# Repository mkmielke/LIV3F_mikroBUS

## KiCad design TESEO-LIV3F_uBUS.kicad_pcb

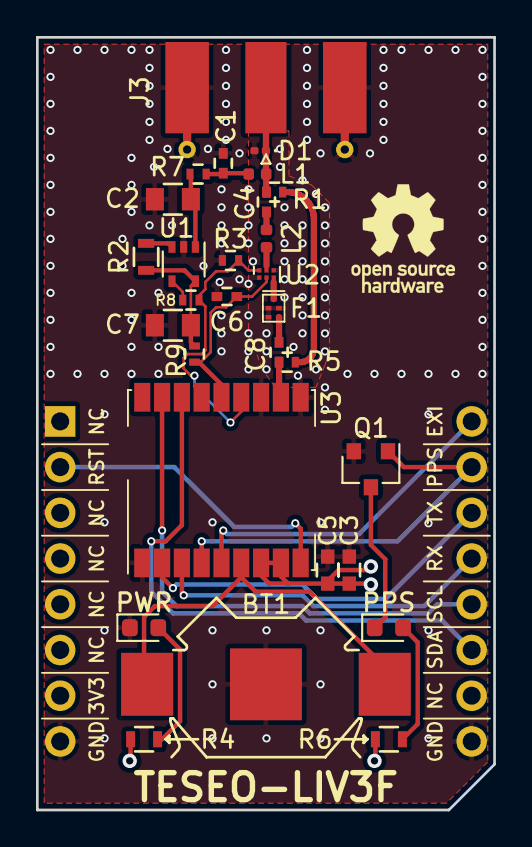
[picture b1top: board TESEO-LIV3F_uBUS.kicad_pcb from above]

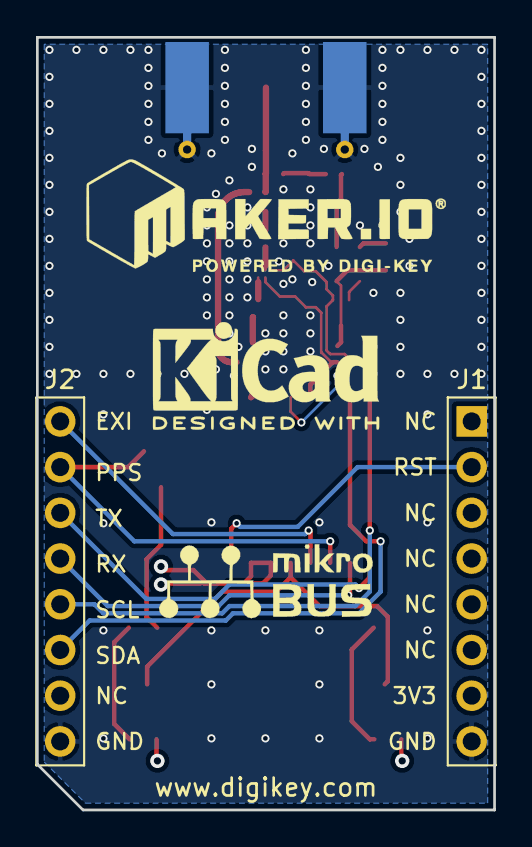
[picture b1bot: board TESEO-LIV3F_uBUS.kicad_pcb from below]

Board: 4 copper layers, 25.4 x 42.9 mm, 31 parts (2 on the bottom side), 27 nets.

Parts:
BT1: Battery_Cell; Keystone_3030_1x10mm-CoinCell
C1: 56p; C_0402
C2: 1u; C_0805
C3: 100p; C_0603
C4, C8: 120p; C_0402
C5: 100n; C_0603
C6: 1n; C_0402
C7: 2.2u; C_0805
D1: D_TVS_ALT; D_0201_0603Metric
D2: LTST-C190KGKT; D_0603_1608Metric
D3: LTST-C190KRKT; D_0603_1608Metric
F1: B4327; Filter_1411-5_1.4x1.1mm
J1, J2: Conn_01x08; PinHeader_1x08_P2.54mm_Vertical
J3: Conn_Coaxial; SMA_Molex_73251-1153_EdgeMount_Horizontal
L1: 56n; L_0402_1005Metric
L2: 6.8n; L_0402_1005Metric
Q1: MMUN2211LT1G; SOT-23
R1, R5, R7, R8, R9: 0; R_0402
R2: 100k; R_0603
R3: 10k; R_0402
R4, R6: 330; R_0603
U1: TPS22943; SOT-353_SC-70-5
U2: BGA725L6; TSNP-6_0.8x0.7mm_P0.4mm
U3: TESEO-LIV3F; TESEO_LIV3F_SMD

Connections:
+3V3: C3.2, C5.2, J1.7, R4.1, R6.1, U3.7, U3.8
+BATT: BT1.1, U3.6
/ANT_OFF: R3.2, R8.2, U2.6, U3.13
/EXI: J2.1, U3.5
/PPS: J2.2, Q1.1, U3.4
/RESET: J1.2, U3.9
/RF_IN: C8.1, R5.1, U3.11
/RX: J2.4, U3.3
/SCL: J2.5, U3.17
/SDA: J2.6, U3.16
/TX: J2.3, U3.2
/VCC_RF: C6.1, R9.2, U2.2, U3.14
GND: BT1.2, C1.2, C2.2, C3.1, C5.1, C6.2, C7.2, D1.2, D2.1, F1.2, F1.3, F1.5, J1.8, J2.8, J3.2, Q1.2, R3.1, U1.2, U2.1, U2.4, U3.1, U3.10, U3.12
unnamed: C1.1, L1.2, R7.2
unnamed: C2.1, R7.1, U1.1
unnamed: C4.1, L2.2
unnamed: C4.2, D1.1, J3.1, L1.1, R1.1
unnamed: C7.1, R2.1, R9.1, U1.5
unnamed: C8.2, F1.4
unnamed: D2.2, R4.2
unnamed: D3.1, Q1.3
unnamed: D3.2, R6.2
unnamed: F1.1, U2.3
unnamed: L2.1, U2.5
unnamed: R1.2, R5.2
unnamed: R2.2, U1.3
unnamed: R8.1, U1.4
